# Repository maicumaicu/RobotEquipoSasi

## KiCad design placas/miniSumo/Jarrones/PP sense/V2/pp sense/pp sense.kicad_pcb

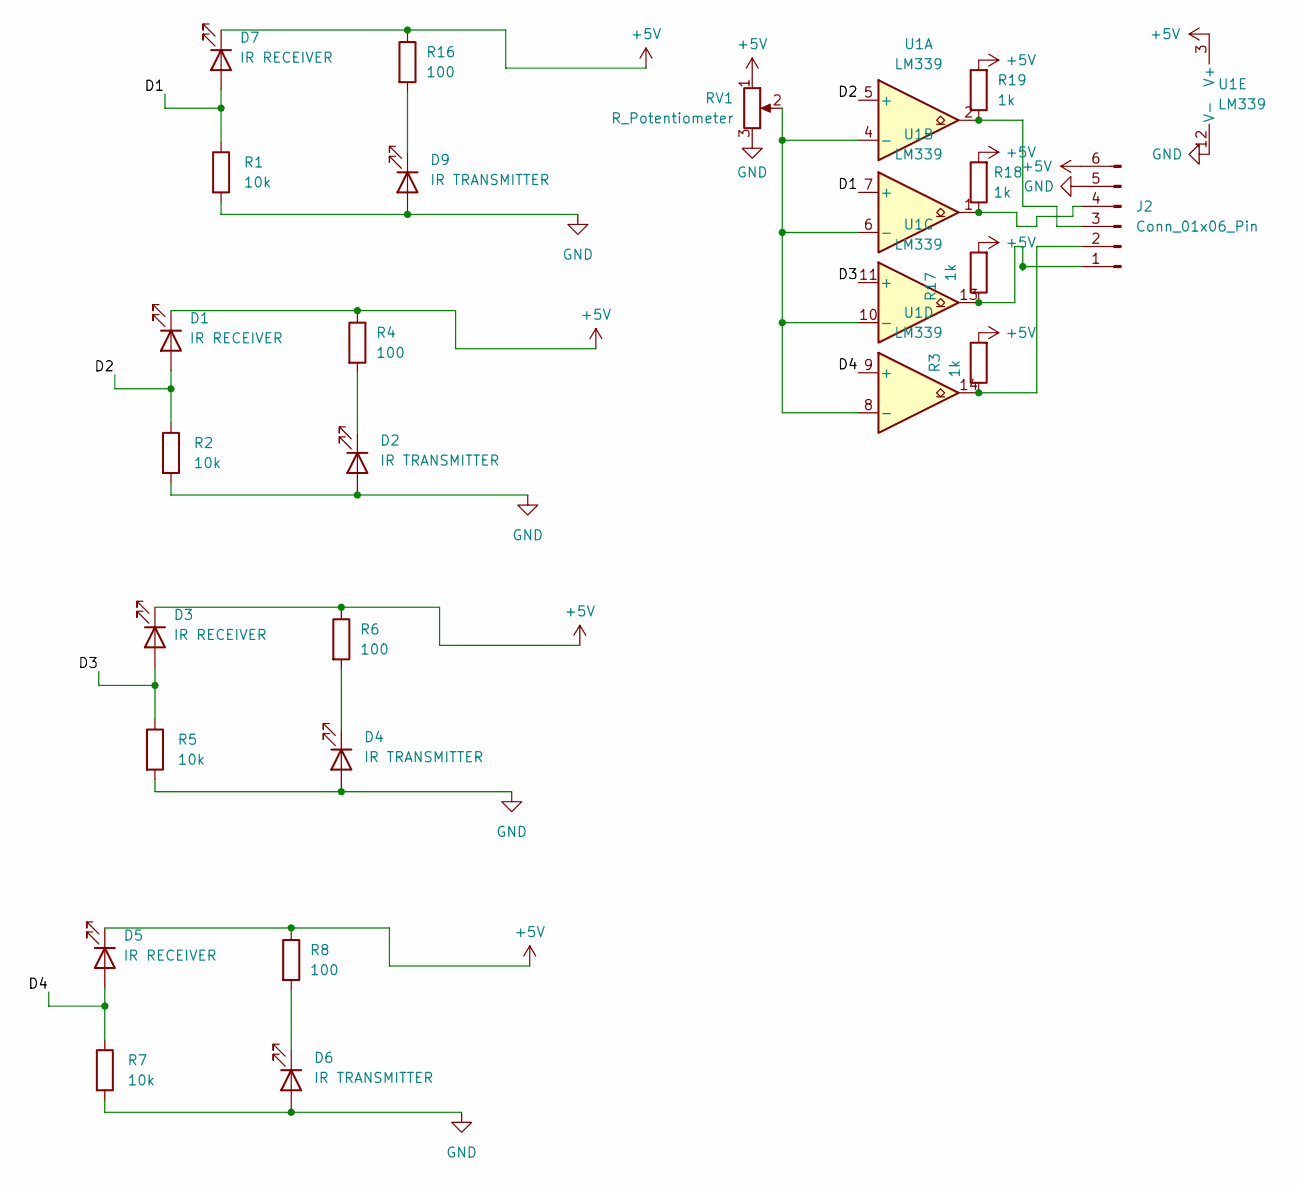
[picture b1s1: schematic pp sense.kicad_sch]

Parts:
D1, D3, D5, D7: IR RECEIVER; LED_D5.0mm
D2, D4, D6, D9: IR TRANSMITTER; LED_D5.0mm
J2: Conn_01x06_Pin; PinHeader_1x06_P2.54mm_Vertical
R1, R2, R5, R7: 10k; R_Axial_DIN0411_L9.9mm_D3.6mm_P5.08mm_Vertical
R3, R17, R18, R19: 1k; R_1206_3216Metric_Pad1.30x1.75mm_HandSolder
R4, R6, R8, R16: 100; R_1206_3216Metric_Pad1.30x1.75mm_HandSolder
RV1: R_Potentiometer; Potentiometer_Bourns_3299W_Vertical
U1: LM339; DIP-14_W7.62mm

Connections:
+5V: D1.1 (K), D3.1 (K), D5.1 (K), D7.1 (K), J2.6, R3.2, R4.1, R6.1, R8.1, R16.1, R17.2, R18.2, R19.2, RV1.1, U1.3 (V+)
/D1: D7.2 (A), R1.1, U1.7 (+)
/D2: D1.2 (A), R2.1, U1.5 (+)
/D3: D3.2 (A), R5.1, U1.11 (+)
/D4: D5.2 (A), R7.1, U1.9 (+)
GND: D2.2 (A), D4.2 (A), D6.2 (A), D9.2 (A), J2.5, R1.2, R2.2, R5.2, R7.2, RV1.3, U1.12 (V-)
unnamed: D2.1 (K), R4.2
unnamed: D4.1 (K), R6.2
unnamed: D6.1 (K), R8.2
unnamed: D9.1 (K), R16.2
unnamed: J2.1, R17.1, U1.13
unnamed: J2.2, R3.1, U1.14
unnamed: J2.3, R19.1, U1.2
unnamed: J2.4, R18.1, U1.1
unnamed: RV1.2, U1.4 (-), U1.6 (-), U1.8 (-), U1.10 (-)

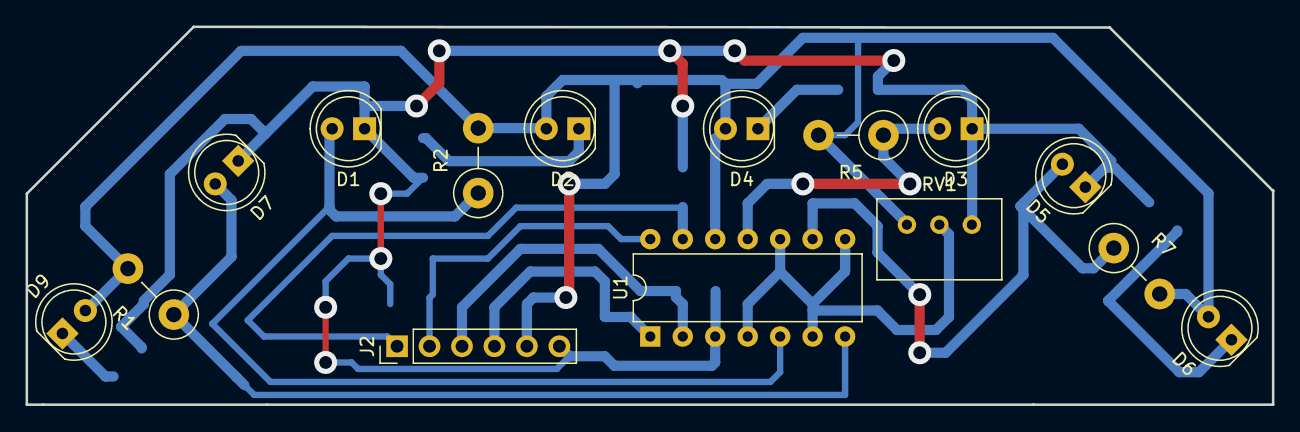
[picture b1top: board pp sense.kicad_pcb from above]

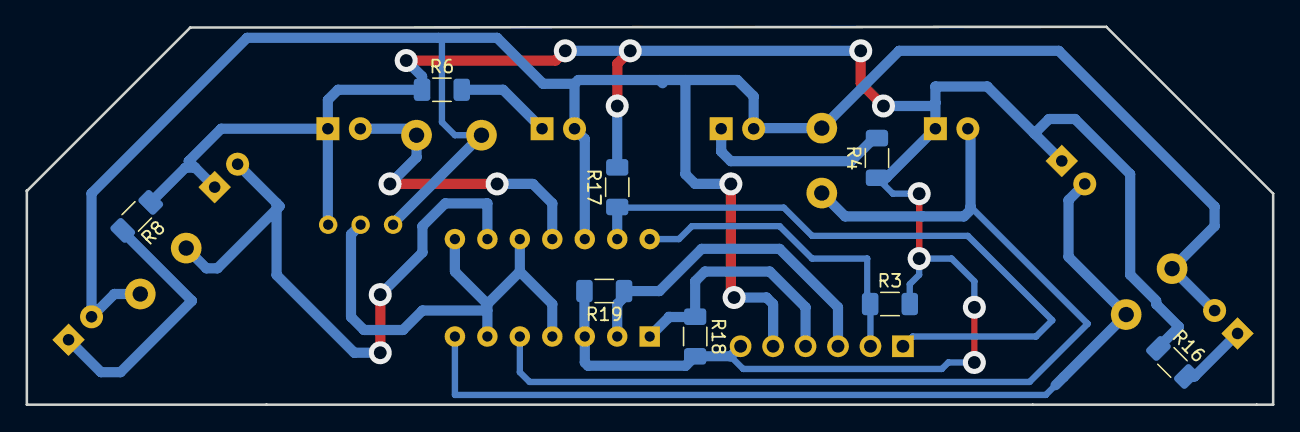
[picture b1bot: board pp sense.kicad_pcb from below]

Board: 2 copper layers, 97.5 x 29.6 mm, 23 parts (8 on the bottom side), 15 nets.

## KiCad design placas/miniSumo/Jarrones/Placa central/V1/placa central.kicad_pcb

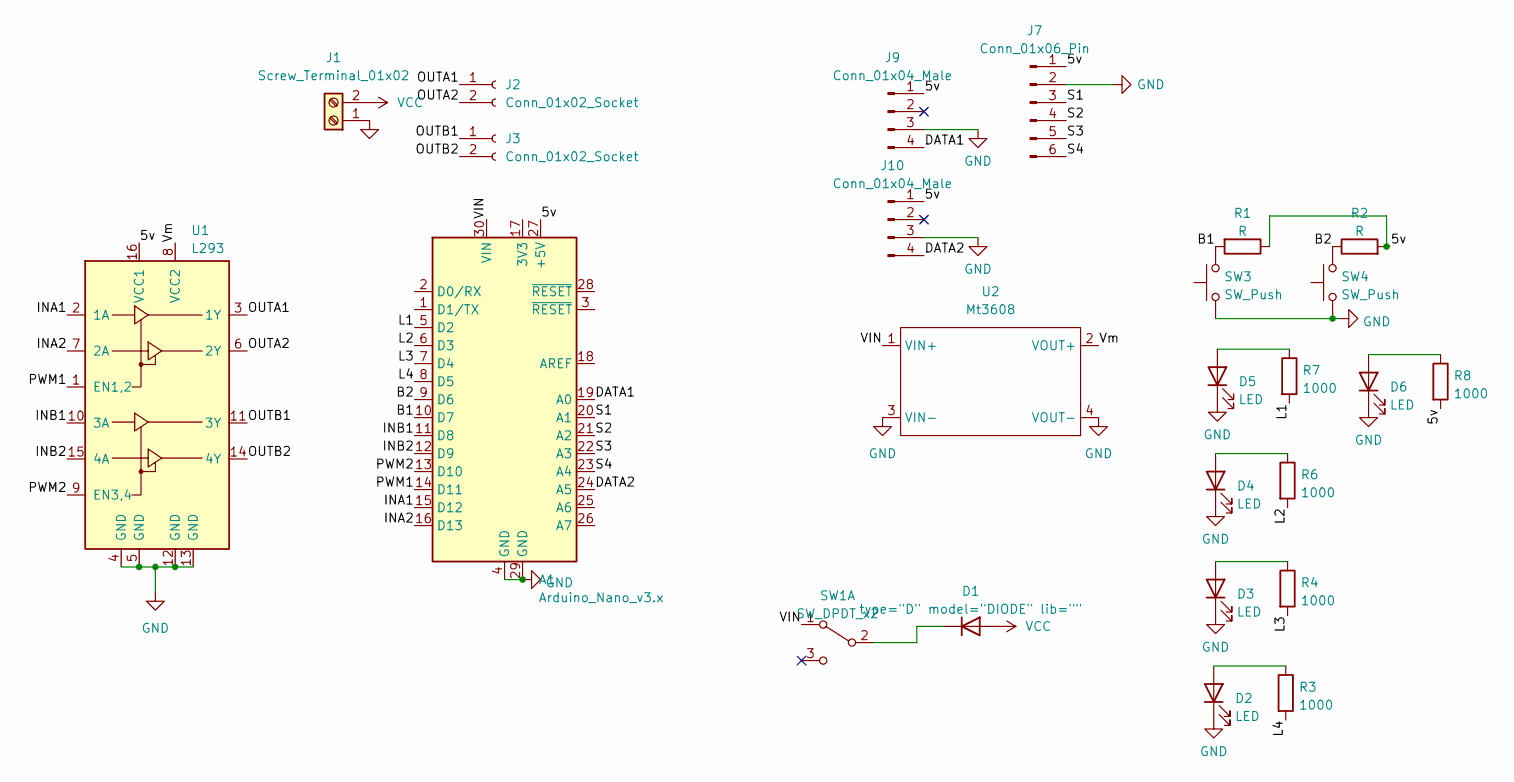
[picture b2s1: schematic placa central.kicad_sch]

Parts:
A1: Arduino_Nano_v3.x; Arduino_Nano
D1: type="D" model="DIODE" lib=""; D_5W_P5.08mm_Vertical_AnodeUp
D2, D3, D4, D5, D6: LED; LED_D3.0mm
J1: Screw_Terminal_01x02; PinSocket_1x02_P2.54mm_Vertical
J2, J3: Conn_01x02_Socket; PinSocket_1x02_P2.54mm_Vertical
J7: Conn_01x06_Pin; PinHeader_1x06_P2.54mm_Vertical
J9, J10: Conn_01x04_Male; PinHeader_1x04_P2.54mm_Vertical
R1, R2: R; R_1206_3216Metric_Pad1.30x1.75mm_HandSolder
R3, R4, R6, R7, R8: 1000; R_1206_3216Metric_Pad1.30x1.75mm_HandSolder
SW1: SW_DPDT_x2; SW_Slide_1P2T_CK_OS102011MS2Q
SW3, SW4: SW_Push; SW_PUSH_6mm
U1: L293; DIP-16_W7.62mm
U2: Mt3608; MT3608

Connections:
/5v: A1.27 (+5V), J7.1, J9.1, J10.1, R1.1, R2.2, R8.2, U1.16 (VCC1)
/B1: A1.10 (D7), R1.2, SW3.2
/B2: A1.9 (D6), R2.1, SW4.2
/DATA1: A1.19 (A0), J9.4
/DATA2: A1.24 (A5), J10.4
/INA1: A1.15 (D12), U1.2 (1A)
/INA2: A1.16 (D13), U1.7 (2A)
/INB1: A1.11 (D8), U1.10 (3A)
/INB2: A1.12 (D9), U1.15 (4A)
/L1: A1.5 (D2), R7.2
/L2: A1.6 (D3), R6.2
/L3: A1.7 (D4), R4.2
/L4: A1.8 (D5), R3.2
/OUTA1: J2.1, U1.3 (1Y)
/OUTA2: J2.2, U1.6 (2Y)
/OUTB1: J3.1, U1.11 (3Y)
/OUTB2: J3.2, U1.14 (4Y)
/PWM1: A1.14 (D11), U1.1 (EN1,2)
/PWM2: A1.13 (D10), U1.9 (EN3,4)
/S1: A1.20 (A1), J7.3
/S2: A1.21 (A2), J7.4
/S3: A1.22 (A3), J7.5
/S4: A1.23 (A4), J7.6
/VIN: A1.30 (VIN), SW1.1 (A), U2.1 (VIN+)
/Vm: U1.8 (VCC2), U2.2 (VOUT+)
GND: A1.4 (GND), A1.29 (GND), D2.1 (K), D3.1 (K), D4.1 (K), D5.1 (K), D6.1 (K), J1.1, J7.2, J9.3, J10.3, SW3.1, SW4.1, U1.4 (GND), U1.5 (GND), U1.12 (GND), U1.13 (GND), U2.3 (VIN-), U2.4 (VOUT-)
unnamed: D1.2 (K), SW1.2 (B)
unnamed: D2.2 (A), R3.1
unnamed: D3.2 (A), R4.1
unnamed: D4.2 (A), R6.1
unnamed: D5.2 (A), R7.1
unnamed: D6.2 (A), R8.1
VCC: D1.1 (A), J1.2

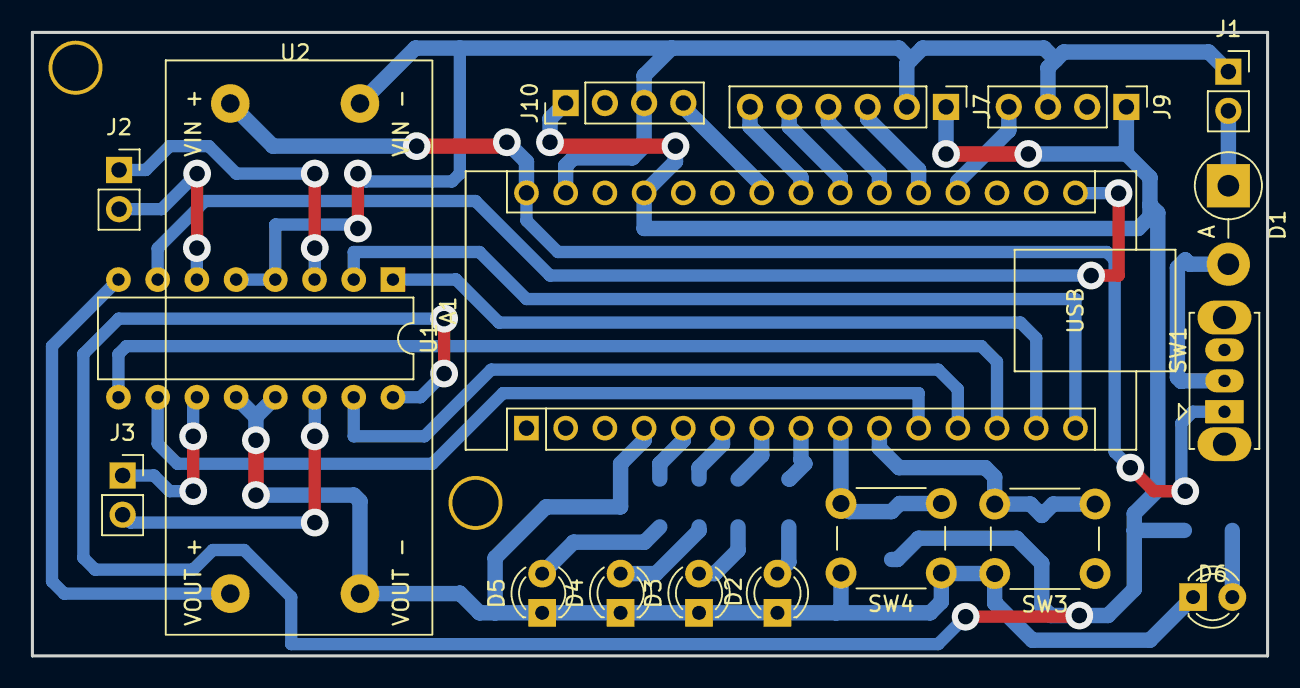
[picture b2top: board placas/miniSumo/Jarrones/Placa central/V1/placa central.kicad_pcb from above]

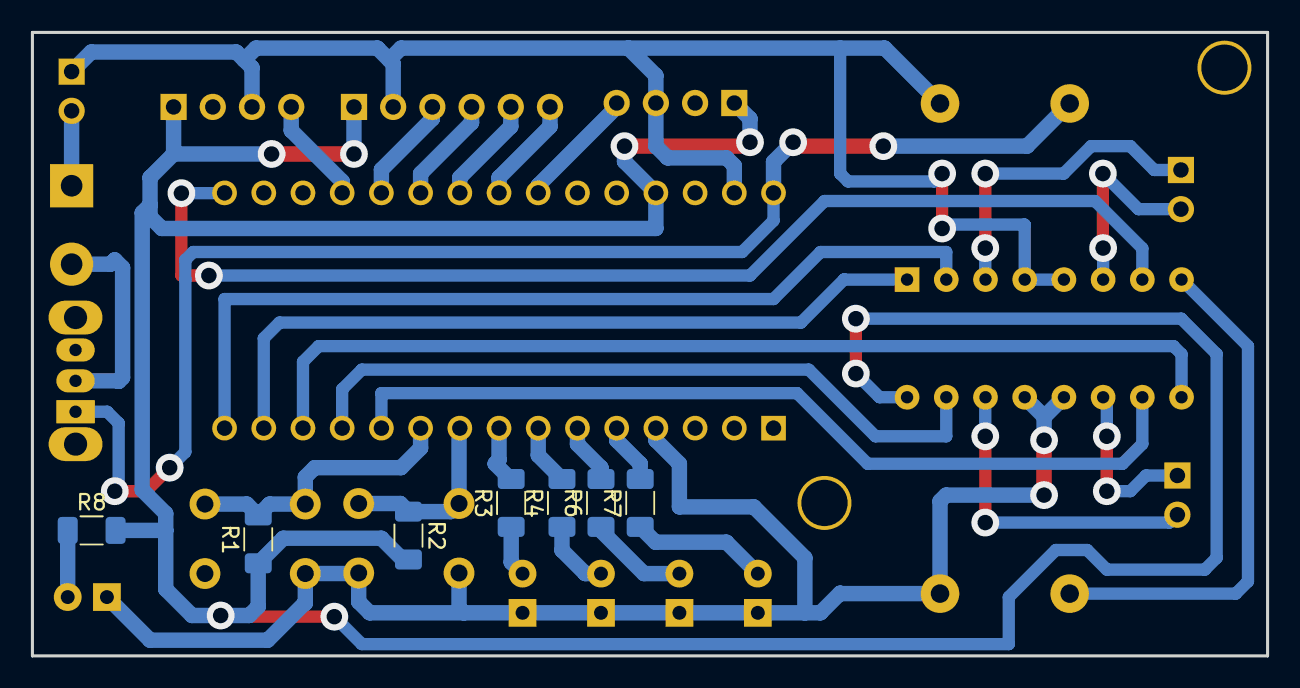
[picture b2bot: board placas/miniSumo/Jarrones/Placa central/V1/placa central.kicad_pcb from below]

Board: 2 copper layers, 80.0 x 40.4 mm, 25 parts (7 on the bottom side), 33 nets.

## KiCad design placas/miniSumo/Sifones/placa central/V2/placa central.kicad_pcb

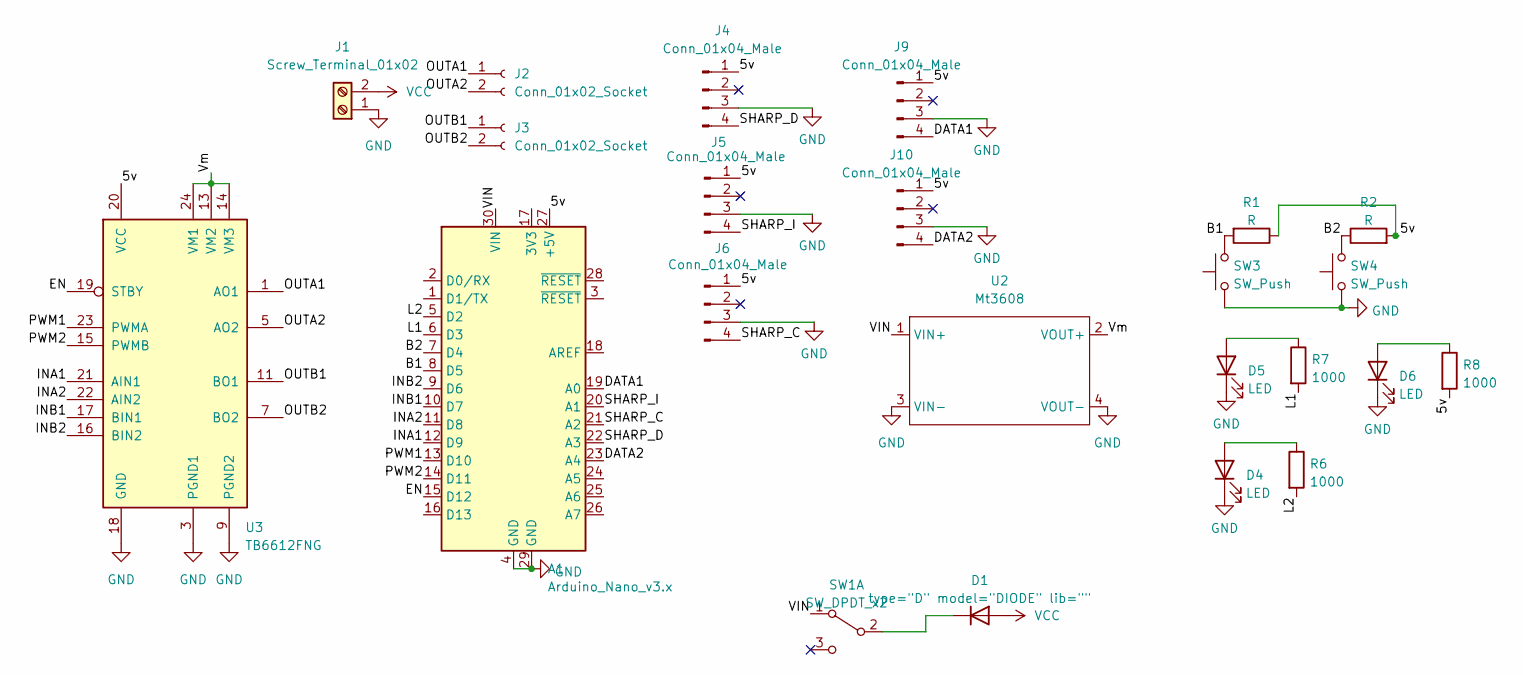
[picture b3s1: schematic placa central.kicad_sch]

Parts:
A1: Arduino_Nano_v3.x; Arduino_Nano
D1: type="D" model="DIODE" lib=""; D_SOD-123
D4, D5, D6: LED; LED_1210_3225Metric
J1: Screw_Terminal_01x02; PinSocket_1x02_P2.54mm_Vertical
J2, J3: Conn_01x02_Socket; PinSocket_1x02_P2.54mm_Vertical
J4, J5, J6, J9, J10: Conn_01x04_Male; PinHeader_1x04_P2.54mm_Vertical
R1, R2: R; R_1210_3225Metric
R6, R7, R8: 1000; R_1210_3225Metric
SW1: SW_DPDT_x2; SW_Slide_1P2T_CK_OS102011MS2Q
SW3, SW4: SW_Push; SW_Push_SPST_NO_Alps_SKRK
U2: Mt3608; MT3608
U3: TB6612FNG; SSOP-24_5.3x8.2mm_P0.65mm

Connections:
/5v: A1.27 (+5V), J4.1, J5.1, J6.1, J9.1, J10.1, R1.1, R2.2, R8.2, U3.20 (VCC)
/B1: A1.8 (D5), R1.2, SW3.2
/B2: A1.7 (D4), R2.1, SW4.2
/DATA1: A1.19 (A0), J9.4
/DATA2: A1.23 (A4), J10.4
/EN: A1.15 (D12), U3.19 (STBY)
/INA1: A1.12 (D9), U3.21 (AIN1)
/INA2: A1.11 (D8), U3.22 (AIN2)
/INB1: A1.10 (D7), U3.17 (BIN1)
/INB2: A1.9 (D6), U3.16 (BIN2)
/L1: A1.6 (D3), R7.2
/L2: A1.5 (D2), R6.2
/OUTA1: J2.1, U3.1 (AO1), U3.2 (AO1)
/OUTA2: J2.2, U3.5 (AO2), U3.6 (AO2)
/OUTB1: J3.1, U3.11 (BO1), U3.12 (BO1)
/OUTB2: J3.2, U3.7 (BO2), U3.8 (BO2)
/PWM1: A1.13 (D10), U3.23 (PWMA)
/PWM2: A1.14 (D11), U3.15 (PWMB)
/SHARP_C: A1.21 (A2), J6.4
/SHARP_D: A1.22 (A3), J4.4
/SHARP_I: A1.20 (A1), J5.4
/VIN: A1.30 (VIN), SW1.1 (A), U2.1 (VIN+)
/Vm: U2.2 (VOUT+), U3.13 (VM2), U3.14 (VM3), U3.24 (VM1)
GND: A1.4 (GND), A1.29 (GND), D4.1 (K), D5.1 (K), D6.1 (K), J1.1, J4.3, J5.3, J6.3, J9.3, J10.3, SW3.1, SW4.1, U2.3 (VIN-), U2.4 (VOUT-), U3.3 (PGND1), U3.4 (PGND1), U3.9 (PGND2), U3.10 (PGND2), U3.18 (GND)
unnamed: D1.2 (K), SW1.2 (B)
unnamed: D4.2 (A), R6.1
unnamed: D5.2 (A), R7.1
unnamed: D6.2 (A), R8.1
VCC: D1.1 (A), J1.2

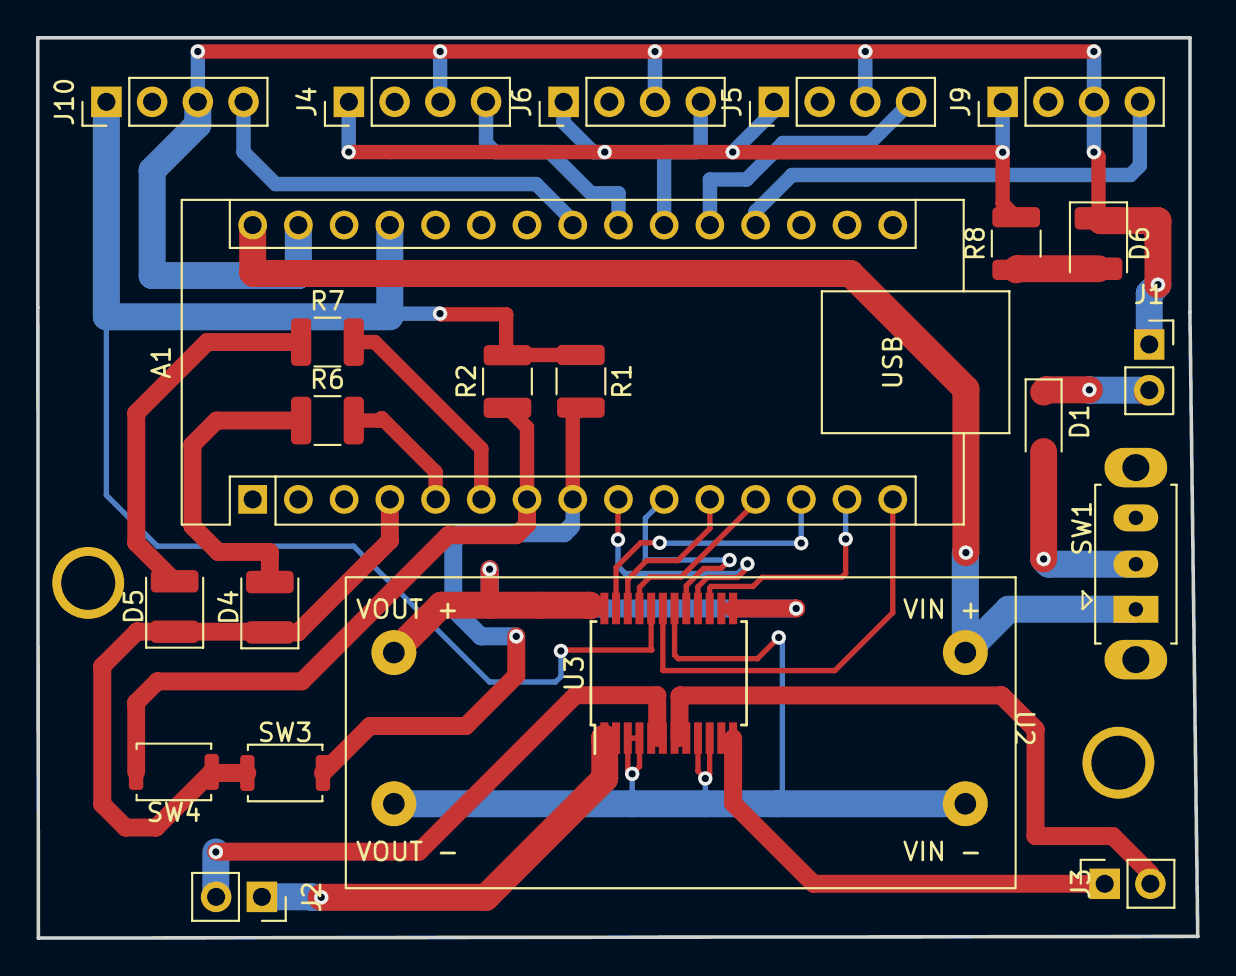
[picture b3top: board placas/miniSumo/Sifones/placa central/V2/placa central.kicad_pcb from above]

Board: 2 copper layers, 64.4 x 50.0 mm, 23 parts (0 on the bottom side), 29 nets.
